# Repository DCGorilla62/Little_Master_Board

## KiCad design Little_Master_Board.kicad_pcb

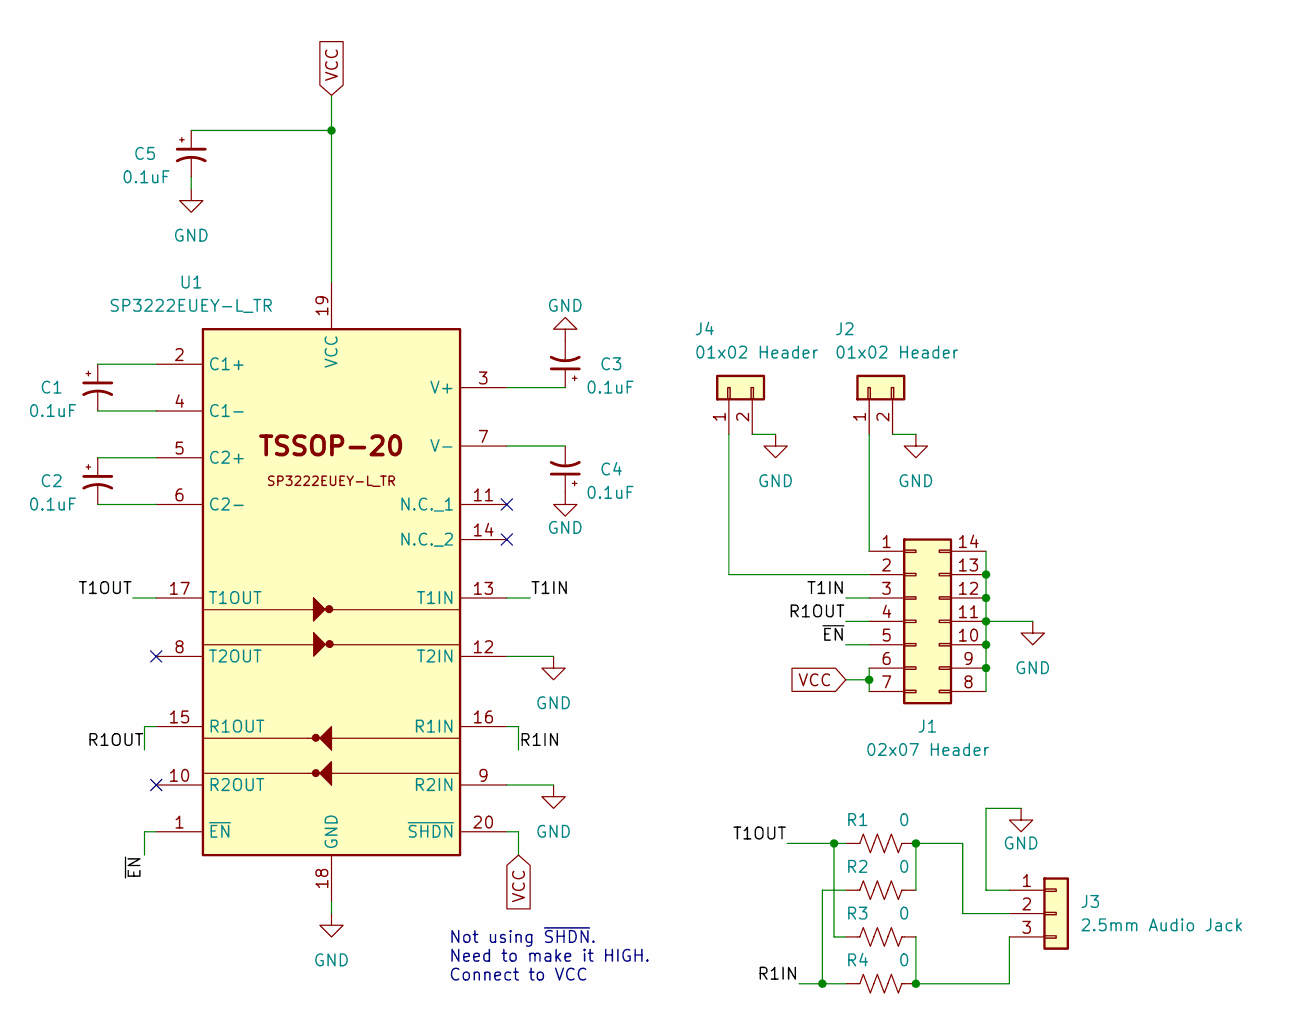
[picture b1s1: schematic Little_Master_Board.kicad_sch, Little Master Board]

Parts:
C1, C2, C3, C4, C5: 0.1uF; C_0402_1005Metric
J1: 02x07 Header; PinHeader_2x07_P2.54mm_Vertical
J2, J4: 01x02 Header; PinHeader_1x02_P2.54mm_Vertical
J3: 2.5mm Audio Jack; SJ1-3513
R1, R2, R3, R4: 0; R_0603_1608Metric
U1: SP3222EUEY-L_TR; SP3222EUEYLTR; Mouser Part Number 701-SP3222EUEY-L/TR

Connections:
/R1IN: R2.1, R4.1, U1.16 (R1IN)
/R1OUT: J1.4, U1.15 (R1OUT)
/T1IN: J1.3, U1.13 (T1IN)
/T1OUT: R1.1, R3.1, U1.17 (T1OUT)
/~EN: J1.5, U1.1 (~EN)
GND: C3.2, C4.1, C5.2, J1.8, J1.9, J1.10, J1.11, J1.12, J1.13, J1.14, J2.2, J3.1, J4.2, U1.9 (R2IN), U1.12 (T2IN), U1.18 (GND)
unnamed: J1.1, J2.1
unnamed: J1.2, J4.1
unnamed: J3.2, R1.2, R2.2
unnamed: J3.3, R3.2, R4.2
unnamed: C1.1, U1.2 (C1+)
unnamed: C1.2, U1.4 (C1-)
unnamed: C2.1, U1.5 (C2+)
unnamed: C2.2, U1.6 (C2-)
unnamed: C3.1, U1.3 (V+)
unnamed: C4.2, U1.7 (V-)
VCC: C5.1, J1.6, J1.7, U1.19 (VCC), U1.20 (~SHDN)

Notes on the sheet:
Not using ~{SHDN}. Need to make it HIGH. Connect to VCC

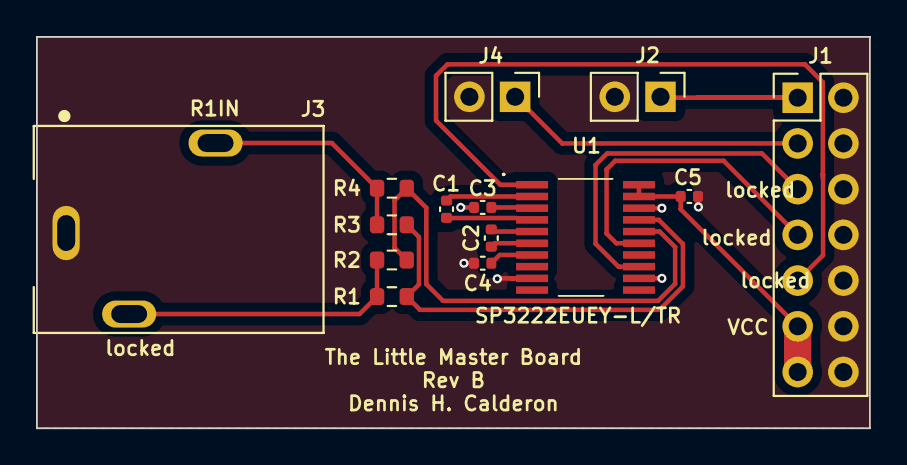
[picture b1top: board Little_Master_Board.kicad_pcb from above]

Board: 2 copper layers, 46.3 x 21.7 mm, 14 parts (0 on the bottom side), 17 nets.

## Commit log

2023-09-21 Updated LMB with feedback from PSA. Created Fabrication files
2023-09-30 Fab files for Rev B updated. Removed SHDN on pin. Connected to VCC for HIGH. Added 2 pin header to pin 2 on 2x7 header. EN routed to pin 5 on 2x7 header.
